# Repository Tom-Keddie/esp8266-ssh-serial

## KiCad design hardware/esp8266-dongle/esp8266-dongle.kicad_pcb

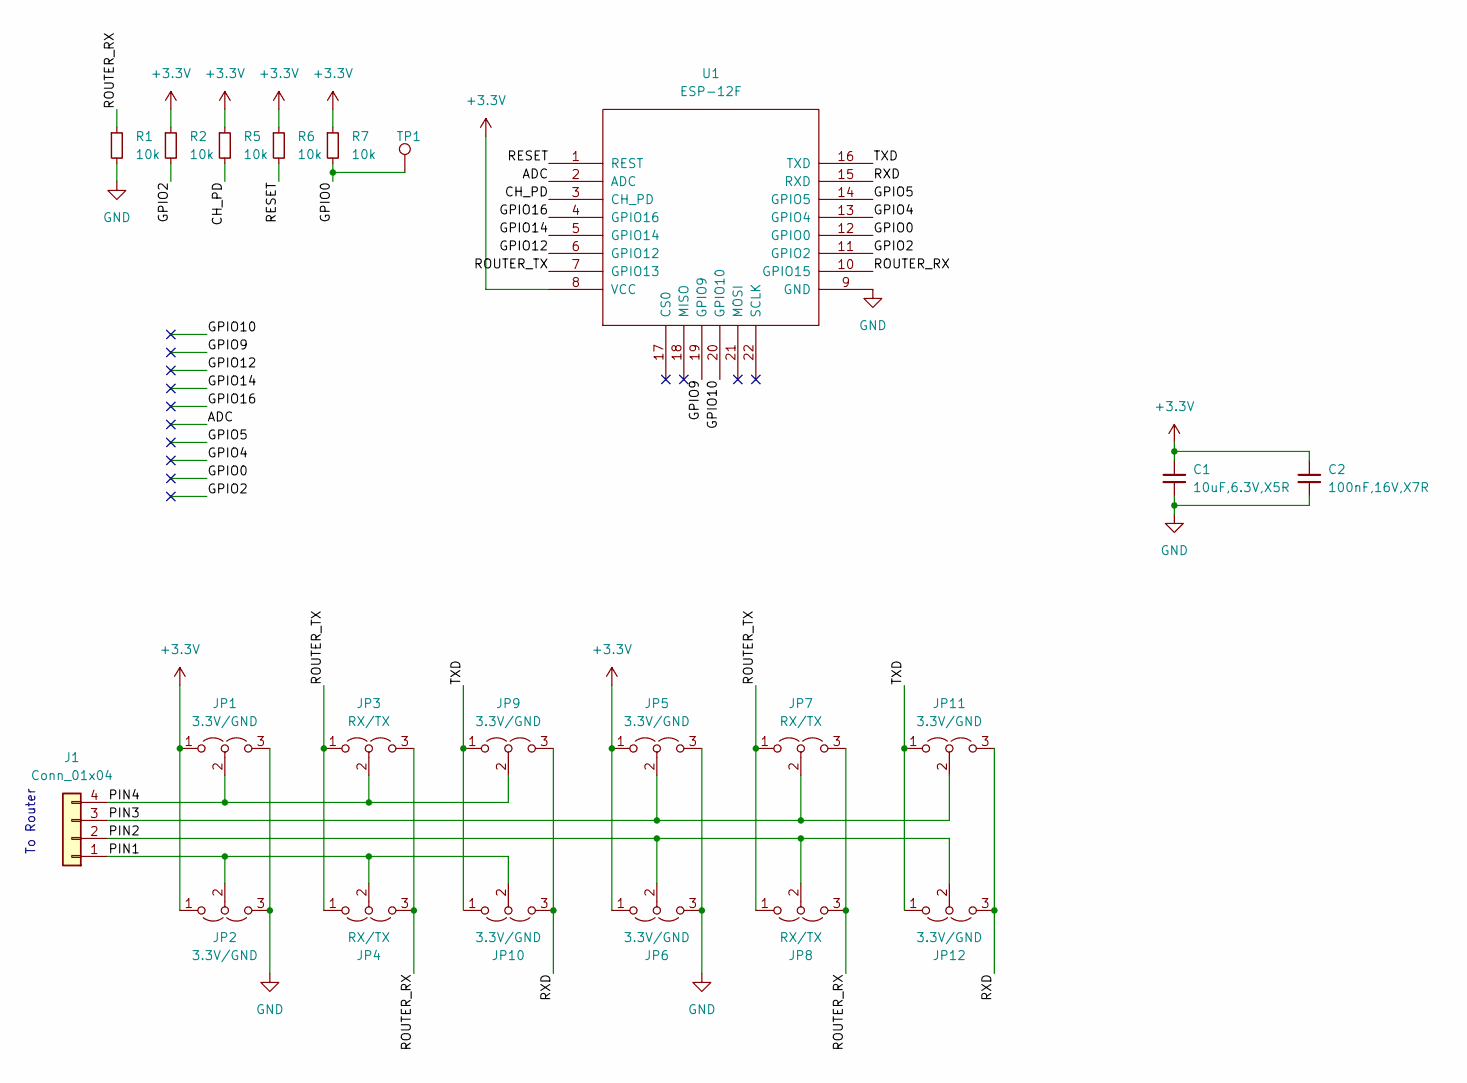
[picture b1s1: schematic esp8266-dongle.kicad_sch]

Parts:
C1: 10uF,6.3V,X5R; C_0402_1005Metric; MFGPN CL05A106MQ5NUNC; LCSC C15525
C2: 100nF,16V,X7R; C_0402_1005Metric; MFGPN CL05B104KO5NNNC; LCSC C1525
J1: Conn_01x04; PinHeader_1x04_P2.54mm_Horizontal
JP1, JP2, JP5, JP6, JP9, JP10, JP11, JP12: 3.3V/GND; SolderJumper-3_P2.0mm_Open_TrianglePad1.0x1.5mm
JP3, JP4, JP7, JP8: RX/TX; SolderJumper-3_P2.0mm_Open_TrianglePad1.0x1.5mm
R1, R2, R5, R6, R7: 10k; R_0402_1005Metric; MFGPN 0402WGF1002TCE; LCSC C25744
TP1: TestPoint; TestPoint_Pad_D1.5mm
U1: ESP-12F; ESP-12E_SMD; LCSC C82891

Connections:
+3V3: C1.1, C2.1, JP1.1 (A), JP2.1 (A), JP5.1 (A), JP6.1 (A), R2.1, R5.1, R6.1, R7.1, U1.8 (VCC)
/ADC: U1.2 (ADC)
/CH_PD: R5.2, U1.3 (CH_PD)
/GPIO0: R7.2, TP1.1, U1.12 (GPIO0)
/GPIO2: R2.2, U1.11 (GPIO2)
/GPIO4: U1.13 (GPIO4)
/GPIO5: U1.14 (GPIO5)
/GPIO9: U1.19 (GPIO9)
/GPIO10: U1.20 (GPIO10)
/GPIO12: U1.6 (GPIO12)
/GPIO14: U1.5 (GPIO14)
/GPIO16: U1.4 (GPIO16)
/PIN1: J1.1, JP2.2 (C), JP4.2 (C), JP10.2 (C)
/PIN2: J1.2, JP6.2 (C), JP8.2 (C), JP12.2 (C)
/PIN3: J1.3, JP5.2 (C), JP7.2 (C), JP11.2 (C)
/PIN4: J1.4, JP1.2 (C), JP3.2 (C), JP9.2 (C)
/RESET: R6.2, U1.1 (REST)
/ROUTER_RX: JP3.3 (B), JP4.3 (B), JP7.3 (B), JP8.3 (B), R1.1, U1.10 (GPIO15)
/ROUTER_TX: JP3.1 (A), JP4.1 (A), JP7.1 (A), JP8.1 (A), U1.7 (GPIO13)
/RXD: JP9.3 (B), JP10.3 (B), JP11.3 (B), JP12.3 (B), U1.15 (RXD)
/TXD: JP9.1 (A), JP10.1 (A), JP11.1 (A), JP12.1 (A), U1.16 (TXD)
GND: C1.2, C2.2, JP1.3 (B), JP2.3 (B), JP5.3 (B), JP6.3 (B), R1.2, U1.9 (GND)

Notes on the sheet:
To Router

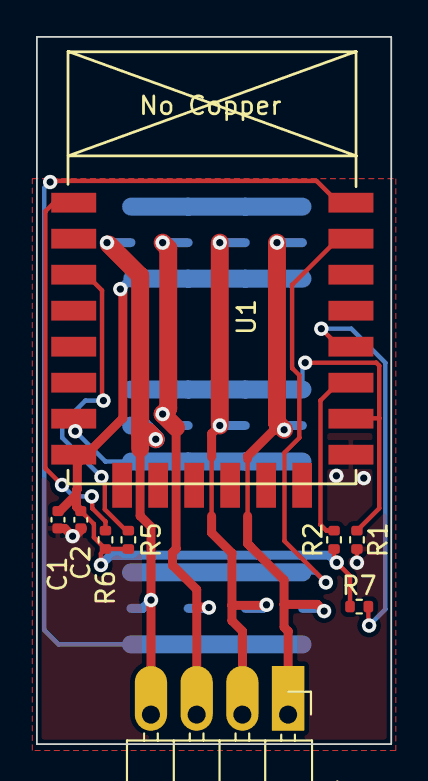
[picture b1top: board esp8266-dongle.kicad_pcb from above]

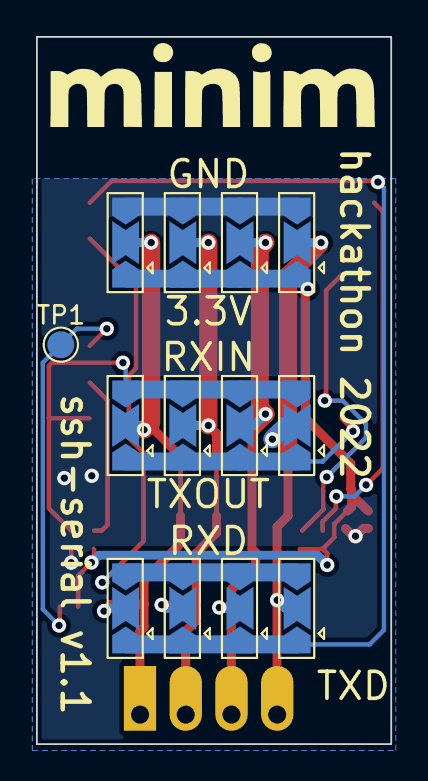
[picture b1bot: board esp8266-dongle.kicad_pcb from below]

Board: 2 copper layers, 19.7 x 39.3 mm, 22 parts (13 on the bottom side), 14 nets.

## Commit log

2022-06-07 kicad: add dongle v1.0, ready to go
2022-08-12 hardware: added gerbers and mfg files
2022-08-12 hardware: add bom
2023-01-28 esp8266-dongle: v1.1 Jan 2023
